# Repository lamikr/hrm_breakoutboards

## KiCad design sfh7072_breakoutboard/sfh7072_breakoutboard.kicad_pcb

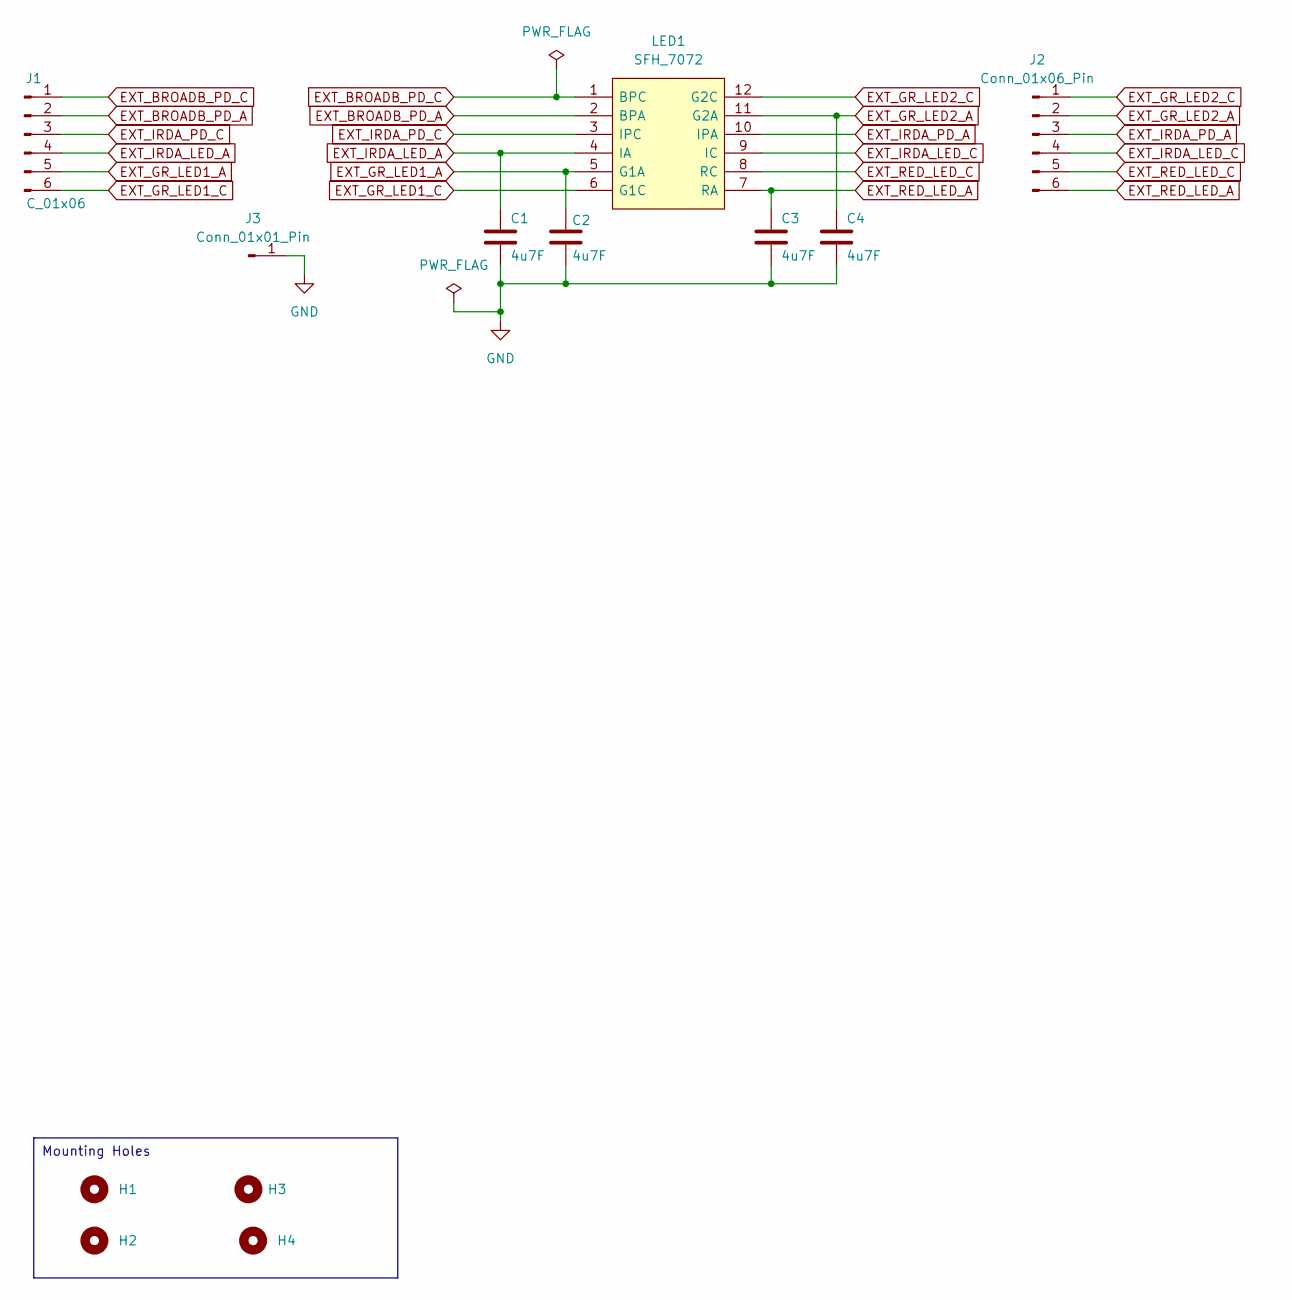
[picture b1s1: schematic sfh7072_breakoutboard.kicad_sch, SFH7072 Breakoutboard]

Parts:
C1, C2, C3, C4: 4u7F; C_0603_1608Metric
H1, H2, H3, H4: MountingHole; PinHeader_1x01_P1.27mm_Vertical
J1: C_01x06; PinHeader_1x06_P2.54mm_Vertical
J2: Conn_01x06_Pin; PinHeader_1x06_P2.54mm_Vertical
J3: Conn_01x01_Pin; PinHeader_1x01_P1.27mm_Vertical
LED1: SFH_7072; SFH7072; Manufacturer_Part_Number SFH 7072; Mouser Part Number 720-SFH7072

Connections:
EXT_BROADB_PD_A: J1.2, LED1.2 (BPA)
EXT_BROADB_PD_C: J1.1, LED1.1 (BPC)
EXT_GR_LED1_A: C2.1, J1.5, LED1.5 (G1A)
EXT_GR_LED1_C: J1.6, LED1.6 (G1C)
EXT_GR_LED2_A: C4.1, J2.2, LED1.11 (G2A)
EXT_GR_LED2_C: J2.1, LED1.12 (G2C)
EXT_IRDA_LED_A: C1.1, J1.4, LED1.4 (IA)
EXT_IRDA_LED_C: J2.4, LED1.9 (IC)
EXT_IRDA_PD_A: J2.3, LED1.10 (IPA)
EXT_IRDA_PD_C: J1.3, LED1.3 (IPC)
EXT_RED_LED_A: C3.1, J2.6, LED1.7 (RA)
EXT_RED_LED_C: J2.5, LED1.8 (RC)
GND: C1.2, C2.2, C3.2, C4.2, J3.1

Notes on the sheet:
Mounting Holes

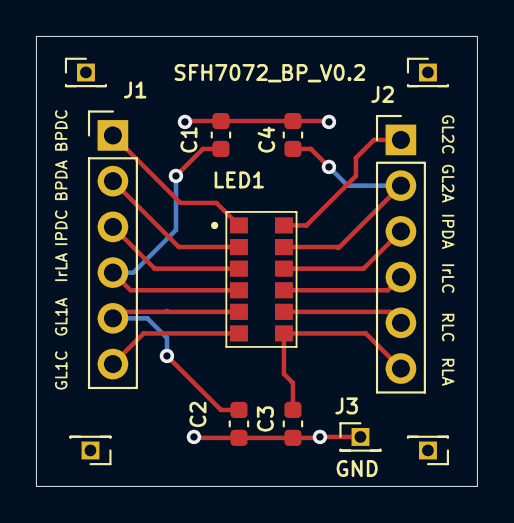
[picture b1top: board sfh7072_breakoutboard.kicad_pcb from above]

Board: 2 copper layers, 24.5 x 25.0 mm, 12 parts (0 on the bottom side), 13 nets.

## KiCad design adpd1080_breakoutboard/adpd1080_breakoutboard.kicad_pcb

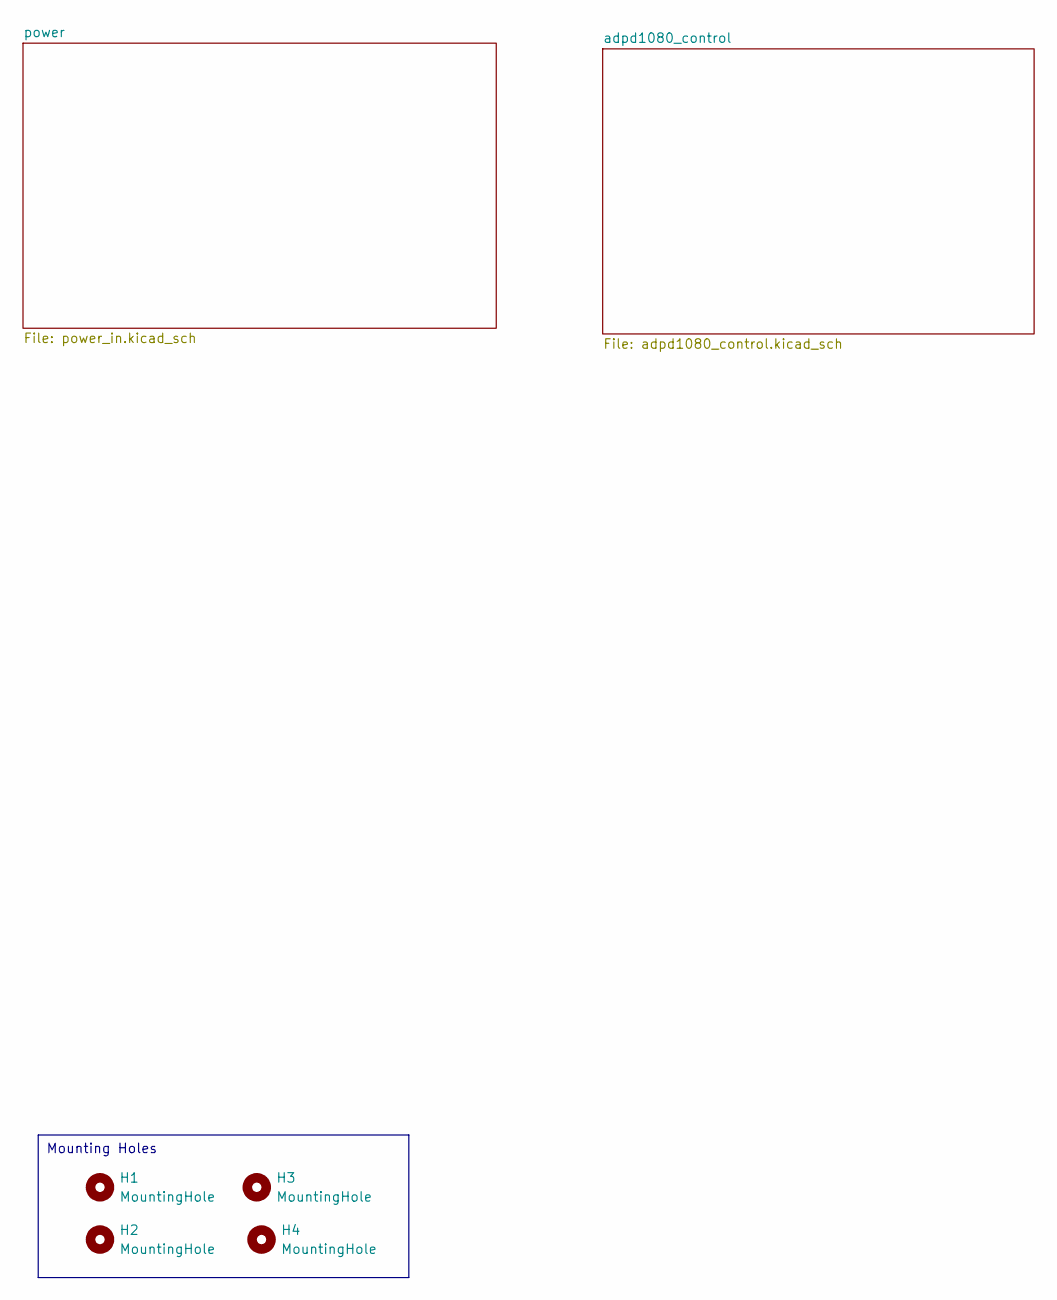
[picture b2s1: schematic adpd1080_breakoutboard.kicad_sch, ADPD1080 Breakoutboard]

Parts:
H1, H2, H3, H4: MountingHole; PinHeader_1x01_P1.27mm_Vertical

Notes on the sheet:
Mounting Holes

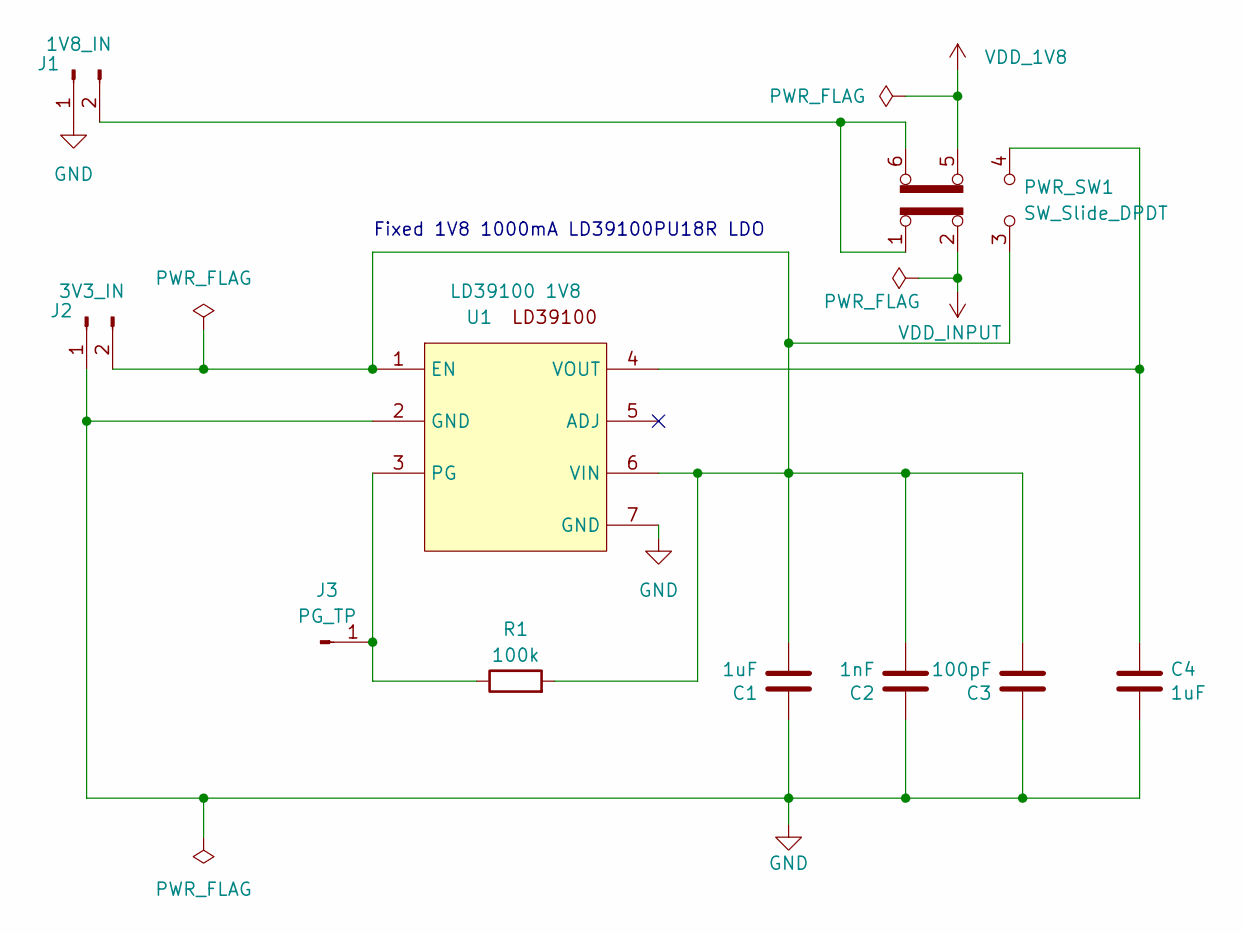
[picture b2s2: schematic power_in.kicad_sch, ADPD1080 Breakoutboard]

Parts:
C1, C4: 1uF; C_0402_1005Metric; MPN GCM188R71E105KA64D
C2: 1nF; C_0402_1005Metric; MPN GCM188R71E105KA64D
C3: 100pF; C_0402_1005Metric; MPN GCM188R71E105KA64D
J1: 1V8_IN; PinHeader_1x02_P2.54mm_Vertical
J2: 3V3_IN; PinHeader_1x02_P2.54mm_Vertical
J3: PG_TP; PinHeader_1x01_P2.54mm_Vertical
PWR_SW1: SW_Slide_DPDT; SW_CK_JS202011CQN_DPDT_Straight
R1: 100k; R_0402_1005Metric
U1: LD39100 1V8; DFN_00PU33R_STM-L

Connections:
GND: C1.1, C2.1, C3.1, C4.2, J1.1, J2.1, U1.2 (GND), U1.7 (GND); also elsewhere on the board
unnamed: J1.2, PWR_SW1.1 (A), PWR_SW1.6 (C)
unnamed: C1.2, C2.2, C3.2, J2.2, PWR_SW1.3 (C), R1.2, U1.1 (EN), U1.6 (VIN)
unnamed: J3.1, R1.1, U1.3 (PG)
unnamed: C4.1, PWR_SW1.4 (A), U1.4 (VOUT)
VDD_1V8: PWR_SW1.5 (B); also elsewhere on the board
VDD_INPUT: PWR_SW1.2 (B); also elsewhere on the board

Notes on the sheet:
Fixed 1V8 1000mA LD39100PU18R LDO

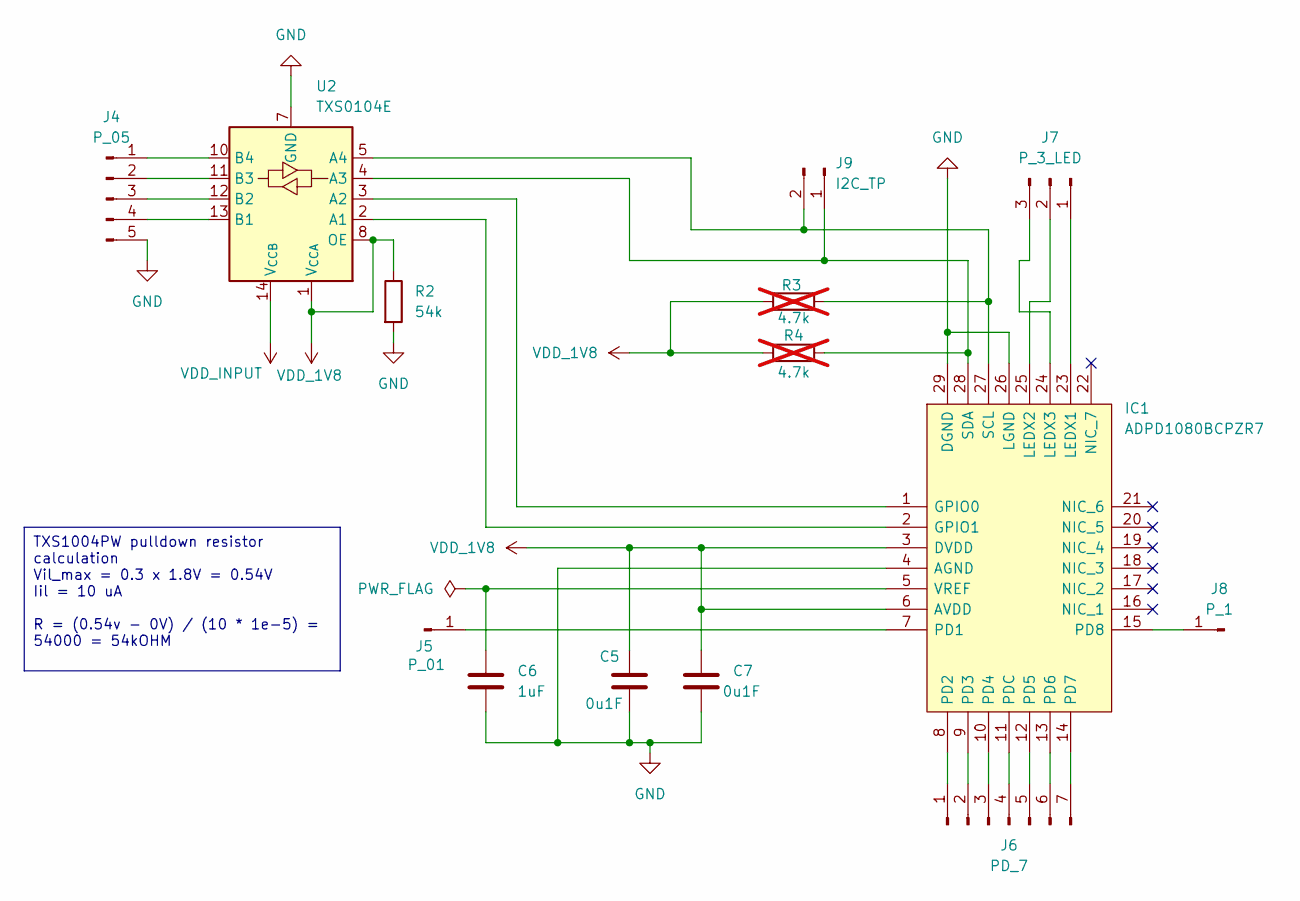
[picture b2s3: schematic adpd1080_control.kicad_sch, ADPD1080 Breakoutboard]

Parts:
C5, C7: 0u1F; C_0402_1005Metric
C6: 1uF; C_0402_1005Metric
IC1: ADPD1080BCPZR7; QFN40P400X400X80-29N-D; Manufacturer_Part_Number ADPD1080BCPZR7; Mouser Part Number 584-ADPD1080BCPZR7
J4: P_05; PinHeader_1x05_P2.54mm_Vertical
J5: P_01; PinHeader_1x01_P2.54mm_Vertical
J6: PD_7; PinHeader_1x07_P2.54mm_Vertical
J7: P_3_LED; PinHeader_1x03_P2.54mm_Vertical
J8: P_1; PinHeader_1x01_P2.54mm_Vertical
J9: I2C_TP; PinHeader_1x02_P1.27mm_Vertical
R2: 54k; R_0402_1005Metric
R3, R4: 4.7k; R_0402_1005Metric; not fitted
U2: TXS0104E; TSSOP-14_4.4x5mm_P0.65mm

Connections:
GND: C5.2, C6.2, C7.2, IC1.4 (AGND), IC1.26 (LGND), IC1.29 (DGND), J4.5, R2.2, U2.7 (GND); also elsewhere on the board
unnamed: IC1.1 (GPIO0), U2.3 (A2)
unnamed: IC1.2 (GPIO1), U2.2 (A1)
unnamed: IC1.23 (LEDX1), J7.1
unnamed: IC1.25 (LEDX2), J7.2
unnamed: IC1.24 (LEDX3), J7.3
unnamed: IC1.7 (PD1), J5.1
unnamed: IC1.8 (PD2), J6.1
unnamed: IC1.9 (PD3), J6.2
unnamed: IC1.10 (PD4), J6.3
unnamed: IC1.12 (PD5), J6.5
unnamed: IC1.13 (PD6), J6.6
unnamed: IC1.14 (PD7), J6.7
unnamed: IC1.15 (PD8), J8.1
unnamed: IC1.11 (PDC), J6.4
unnamed: IC1.27 (SCL), J9.2, R3.2, U2.5 (A4)
unnamed: IC1.28 (SDA), J9.1, R4.2, U2.4 (A3)
unnamed: C6.1, IC1.5 (VREF)
unnamed: J4.1, U2.10 (B4)
unnamed: J4.2, U2.11 (B3)
unnamed: J4.3, U2.12 (B2)
unnamed: J4.4, U2.13 (B1)
VDD_1V8: C5.1, C7.1, IC1.3 (DVDD), IC1.6 (AVDD), R2.1, R3.1, R4.1, U2.1 (V_{CCA}), U2.8 (OE); also elsewhere on the board
VDD_INPUT: U2.14 (V_{CCB}); also elsewhere on the board

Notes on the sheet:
TXS1004PW pulldown resistor calculation Vil_max = 0.3 x 1.8V = 0.54V Iil = 10 uA R = (0.54v - 0V) / (10 * 1e-5) = 54000 = 54kOHM

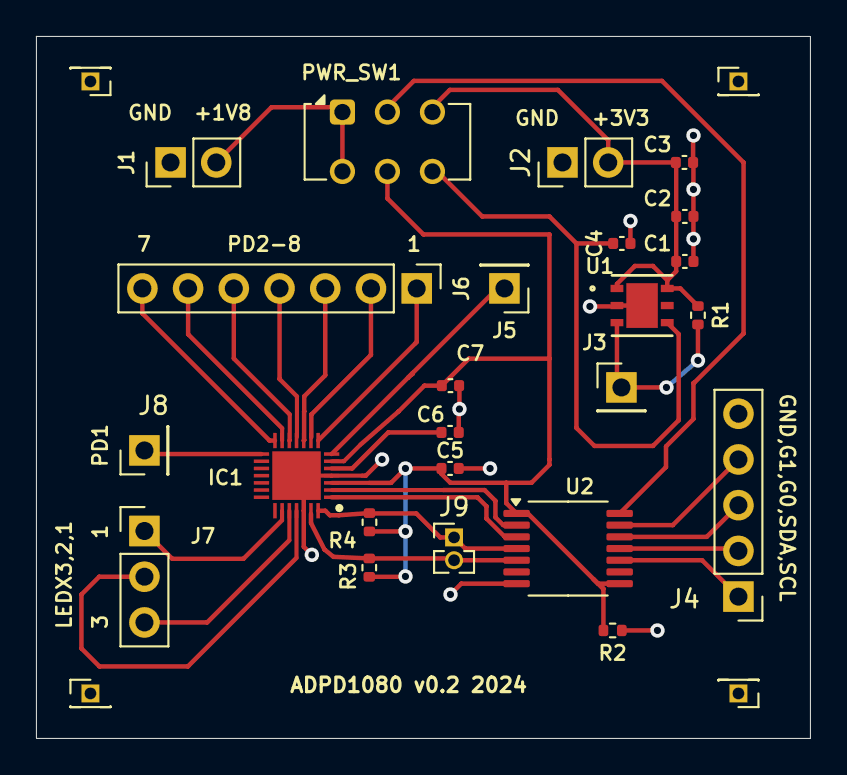
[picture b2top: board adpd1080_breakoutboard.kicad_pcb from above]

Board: 2 copper layers, 43.0 x 39.0 mm, 28 parts (0 on the bottom side), 28 nets.

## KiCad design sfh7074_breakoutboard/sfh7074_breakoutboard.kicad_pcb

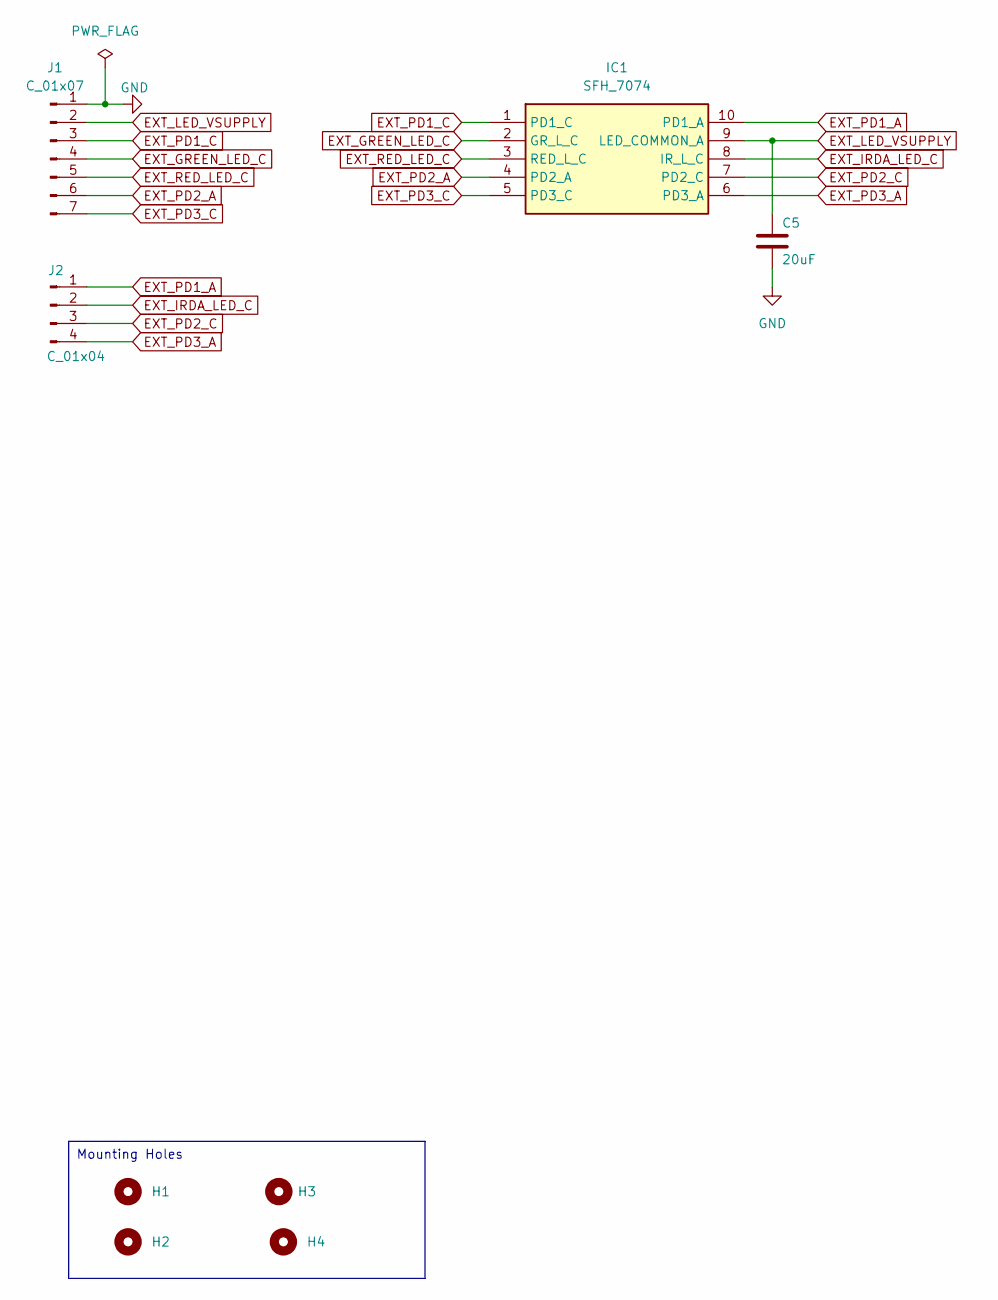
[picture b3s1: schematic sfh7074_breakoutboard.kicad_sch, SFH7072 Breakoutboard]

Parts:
C5: 20uF; C_0603_1608Metric
H1, H2, H3, H4: MountingHole; PinHeader_1x01_P1.27mm_Vertical
IC1: SFH_7074; SFH7074; Mouser Part Number 720-SFH7074
J1: C_01x07; PinHeader_1x07_P2.54mm_Vertical
J2: C_01x04; PinHeader_1x04_P2.54mm_Vertical

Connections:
EXT_GREEN_LED_C: IC1.2 (GR_L_C), J1.4
EXT_IRDA_LED_C: IC1.8 (IR_L_C), J2.2
EXT_LED_VSUPPLY: C5.1, IC1.9 (LED_COMMON_A), J1.2
EXT_PD1_A: IC1.10 (PD1_A), J2.1
EXT_PD1_C: IC1.1 (PD1_C), J1.3
EXT_PD2_A: IC1.4 (PD2_A), J1.6
EXT_PD2_C: IC1.7 (PD2_C), J2.3
EXT_PD3_A: IC1.6 (PD3_A), J2.4
EXT_PD3_C: IC1.5 (PD3_C), J1.7
EXT_RED_LED_C: IC1.3 (RED_L_C), J1.5
GND: C5.2, J1.1

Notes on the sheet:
Mounting Holes

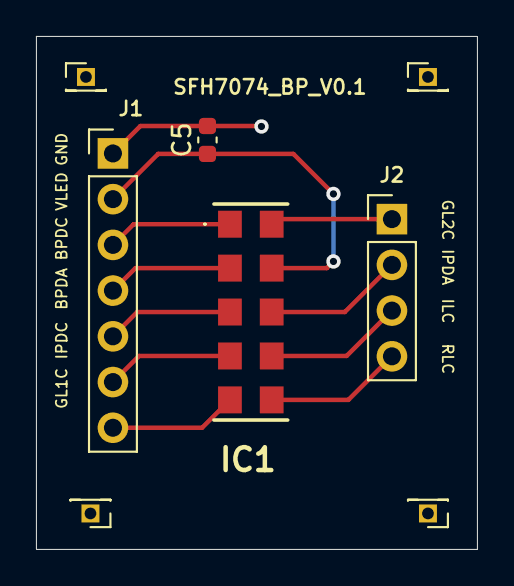
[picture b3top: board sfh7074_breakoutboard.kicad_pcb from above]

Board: 2 copper layers, 24.5 x 28.5 mm, 8 parts (0 on the bottom side), 11 nets.

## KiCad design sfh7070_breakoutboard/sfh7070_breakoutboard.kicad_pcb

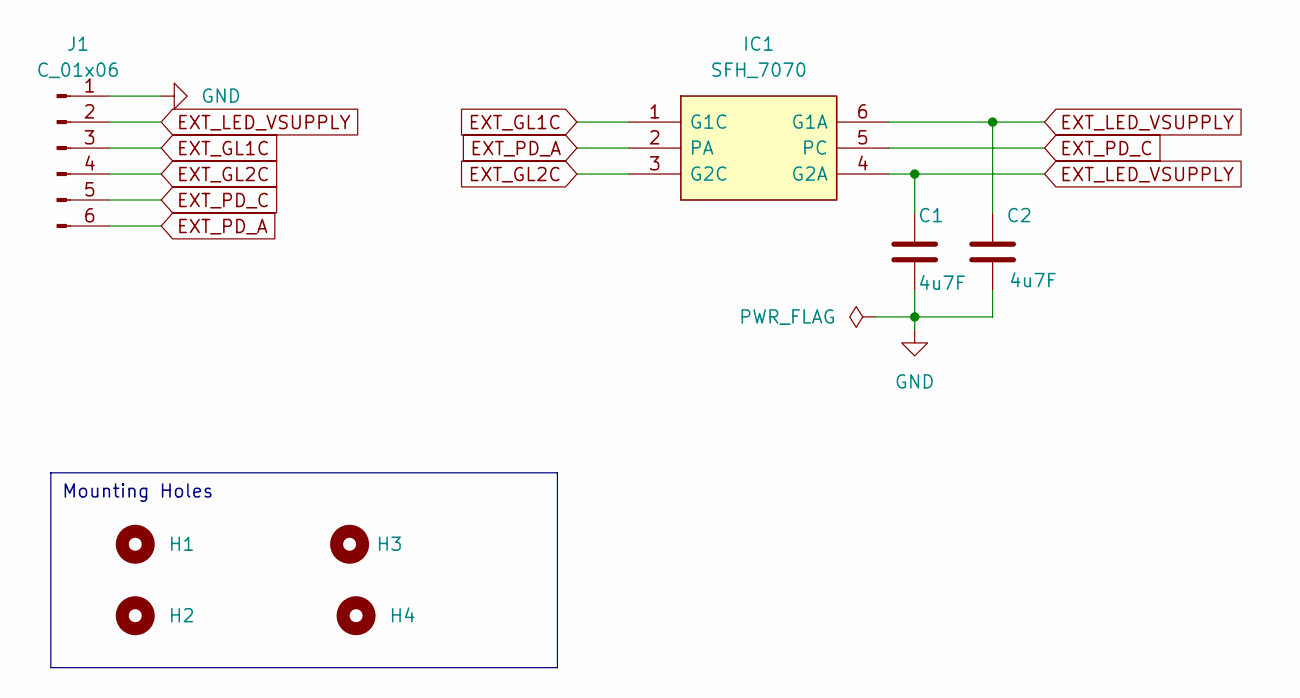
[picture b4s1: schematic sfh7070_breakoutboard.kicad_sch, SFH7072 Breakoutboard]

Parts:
C1, C2: 4u7F; C_0603_1608Metric
H1, H2, H3, H4: MountingHole; PinHeader_1x01_P1.27mm_Vertical
IC1: SFH_7070; SFH7070; Manufacturer_Part_Number SFH 7070; Mouser Part Number 720-SFH7070
J1: C_01x06; PinHeader_1x06_P2.54mm_Vertical

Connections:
EXT_GL1C: IC1.1 (G1C), J1.3
EXT_GL2C: IC1.3 (G2C), J1.4
EXT_LED_VSUPPLY: C1.1, C2.1, IC1.4 (G2A), IC1.6 (G1A), J1.2
EXT_PD_A: IC1.2 (PA), J1.6
EXT_PD_C: IC1.5 (PC), J1.5
GND: C1.2, C2.2, J1.1

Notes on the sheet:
Mounting Holes

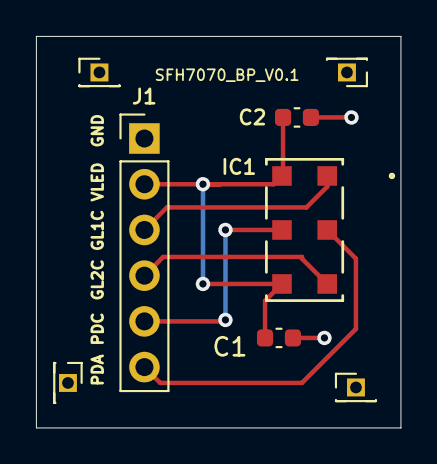
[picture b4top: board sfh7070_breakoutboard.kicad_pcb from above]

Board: 2 copper layers, 20.2 x 21.8 mm, 8 parts (0 on the bottom side), 6 nets.

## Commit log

2024-02-27 adpd1080 breakoutboard
2024-02-28 added sfh7072 breakoutboard
2024-02-29 pdf rename
2024-03-01 removed caps that were in wrong side of ledx
2024-03-01 adpd4101 symbol and footprint
2024-03-01 sfh7072 cap location updates
2024-03-02 component library updates
2024-03-02 adpd1080 pcb manufacturing files
2024-03-02 sfh7070 breakoutboard and pcb manufacturing
2024-03-02 sfh7072 breakoutboard and pcb manufacturing
2024-03-02 sfh7074 breakoutboard and pcb manufacturing
2024-03-02 sfh7072 soldermask -10pct update
2024-03-28 added txs0104e symbol
    - add least the tssop package footprint
    and symbol is pin compatible with the txb0104
2024-03-28 replace txb0104 with txs0104e for i2c
    - txb0104 does not work with i2c but txs0104e works
    - changed the i2c pull-ups to 'no-placement' because
    the txs0104e has internal 10k pull-ups
    - added test points for 1v8 logic scl and sda
2024-03-28 updated bom and gerber files for v0.2 board version
2024-03-29 sfh7072 board with separate anode for all leds
    - separate anode and cathode connector for all leds
    and photodiodes

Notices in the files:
adpd1080_breakoutboard/adpd1080_breakoutboard.kicad_sch:
Copyright (C) 2024, Mika Laitio
